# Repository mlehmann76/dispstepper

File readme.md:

# Dispense steppermotor controller
control a steppermotor to dispense fluids from syringes

4 modes

* Single Mode (dispensing on button, stop + retract after steps, selectable number of steps)
* Repeat Mode (continue dispense on pressed button, retract after button release, selectable number of steps)
* Manual Mode (control direction of stepper motor, selectable speed)
* External Mode (contro over usb serial device)

## Configuration
### By Button
push mode button, selected mode led will lit and settings can be changed by up/down button and led will switch to bar mode showning actual setting (0..3)
### By serial commands
all commands can change to read mode by adding a ?
| Command | Range | Description |
| :-- | :-- | :-- |
| *IDN | | read device version |
| SETup:FACtory:DEFault| 1 |set config to factory defaults |
| SETup:MODE | (0 .. 3) | get / set Mode / Single=0/Repeat=1/Manual=2/External=3 |
| SETup:SINGle:INDex |(0..3) | get / set single mode index |
| SETup:SINGle:VALue# |(0..4096)| get / set single mode value (# is 0..3)  steps |
| SETup:REPeat:INDex |(0..3)| get / set repeat mode index  |
| SETup:REPeat:VALue# |(0..4096)|get / set repeat mode value (# is 0..3) steps |
| SETup:MANual:INDex |(0..3)| get / set manual mode index  |
| SETup:MANual:VALue# |(0..1.0)| get / set manual mode value (# is 0..3) speed |
| SETup:EXTernal:SPeed |(0..1.0)| get / set speed value  for control over serial |
| SETup:EXTernal:STeps |(0..4096)| get / set steps value for control over serial |
| SETup:EXTernal:DIR |(-1, 0, 1)| get / set direction  for control over serial, this will start move if direction not 0. set to 0 after steps |
# Programming
## BootLoader
change into uf2-samdx1
> make BOARD=dispstepper jlink-flash
* now LED D2 should blink
## Application
### via uf2 bootloader
* double tap reset to enter boot loader
* led2 will start blinking
* the board will register as a mass storage device
* put the uf2 update file onto the mass storage and firware update will start

# License
See Microchip / Atmel / Arm source code files for license.

The new code is licensed under MIT.

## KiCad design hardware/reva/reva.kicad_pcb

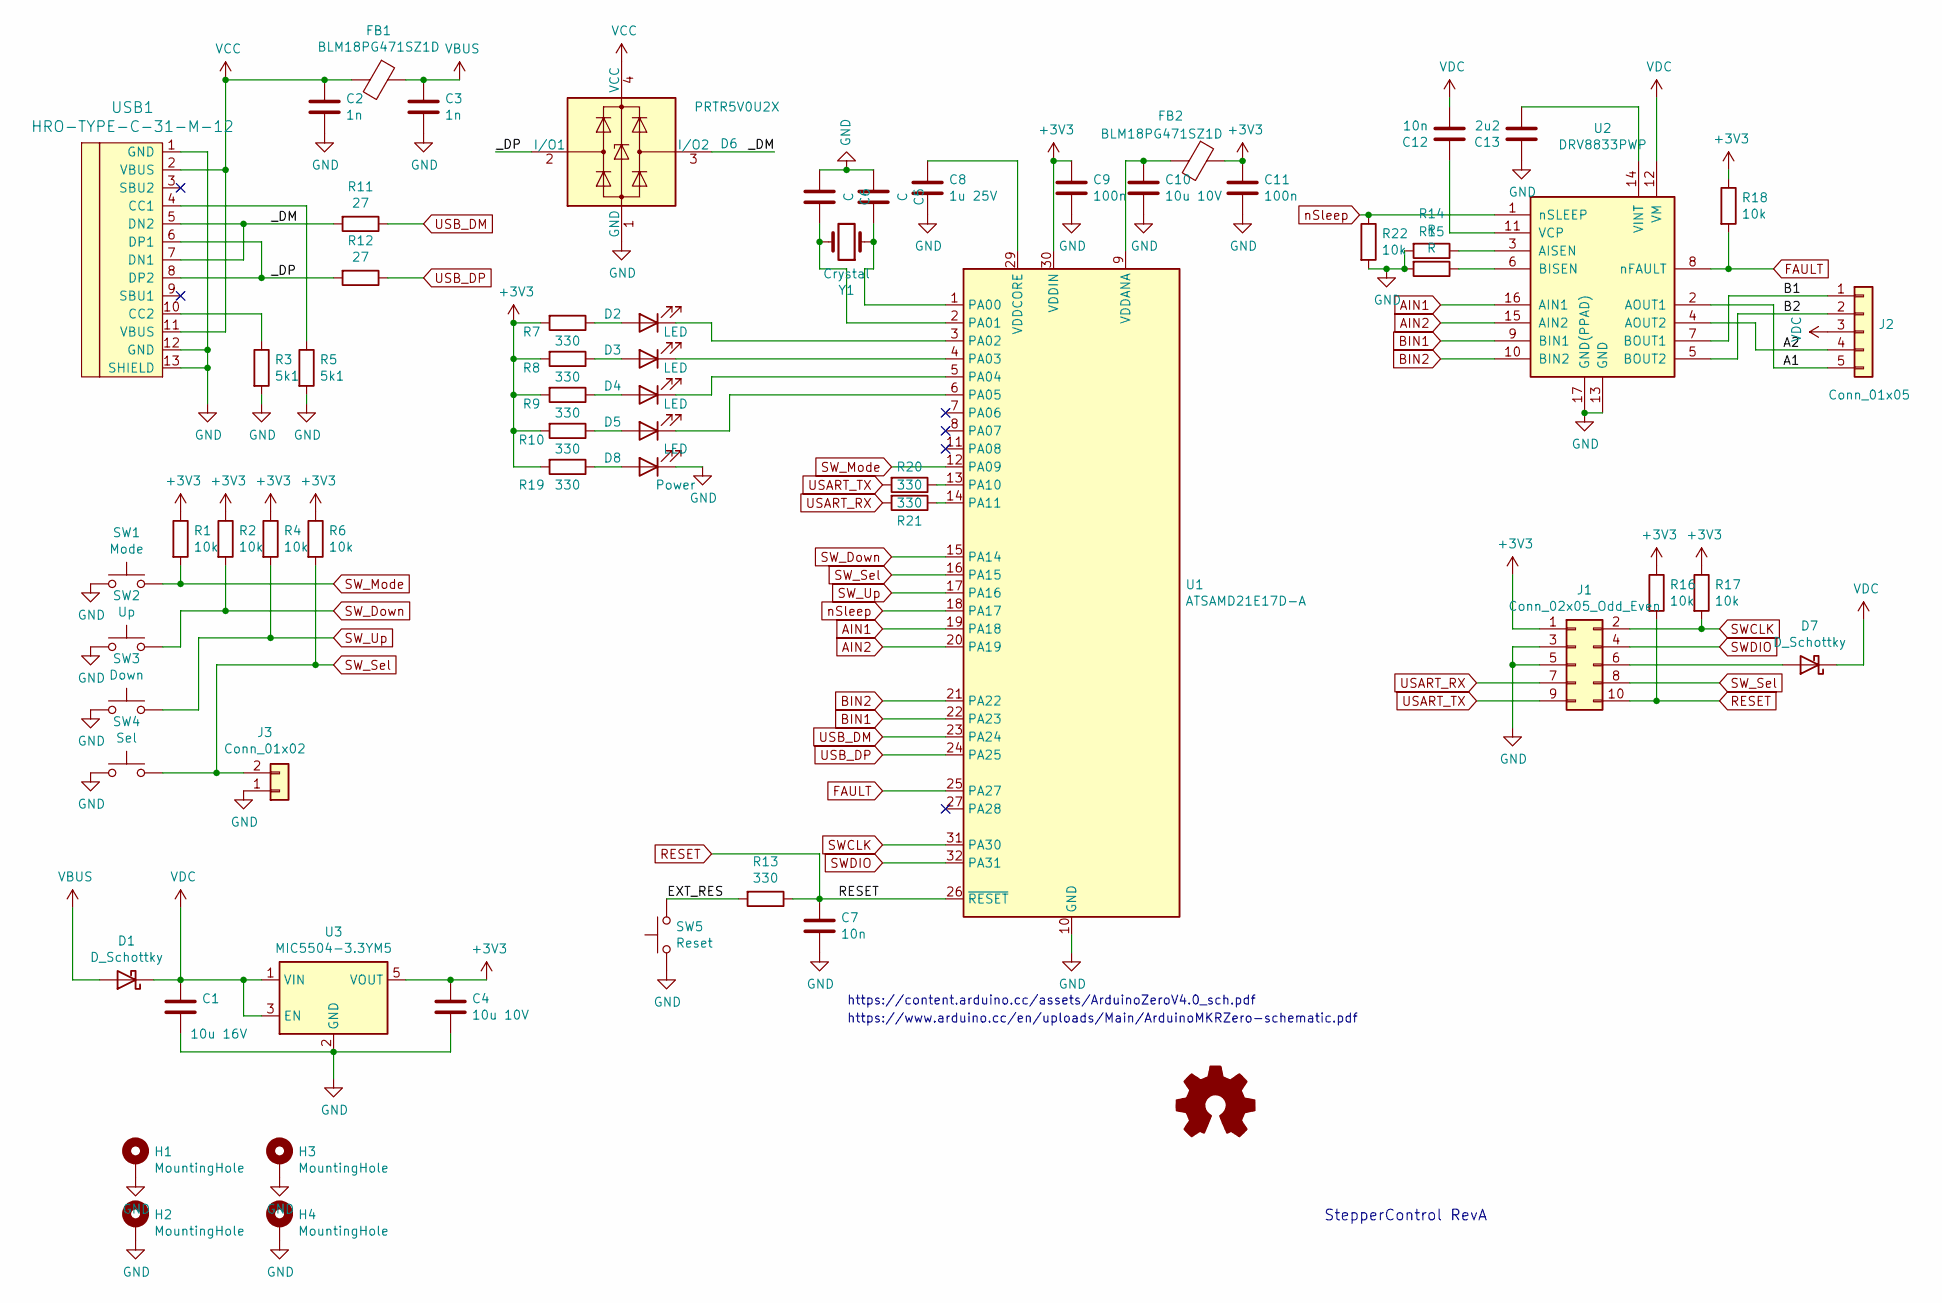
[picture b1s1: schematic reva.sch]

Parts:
C1: 10u 16V; C_0603_1608Metric
C2, C3: 1n; C_0603_1608Metric
C4, C10: 10u 10V; C_0603_1608Metric
C5, C6: C; C_0603_1608Metric
C7, C12: 10n; C_0603_1608Metric
C8: 1u 25V; C_0603_1608Metric
C9, C11: 100n; C_0603_1608Metric
C13: 2u2; C_0603_1608Metric
D1, D7: D_Schottky; D_SMA
D2, D3, D4, D5: LED; LED_0603_1608Metric
D6: PRTR5V0U2X; SOT-143
D8: Power; LED_0603_1608Metric
FB1, FB2: BLM18PG471SZ1D; L_0603_1608Metric
H1, H2, H3, H4: MountingHole; MountingHole_3.2mm_M3_DIN965_Pad
J1: Conn_02x05_Odd_Even; PinHeader_2x05_P2.54mm_Horizontal
J2: Conn_01x05; PinHeader_1x05_P2.54mm_Vertical
J3: Conn_01x02; PinHeader_1x02_P2.54mm_Vertical
R1, R2, R4, R6, R16, R17, R18, R22: 10k; R_0603_1608Metric
R3, R5: 5k1; R_0603_1608Metric
R7, R8, R9, R10, R13, R19, R20, R21: 330; R_0603_1608Metric
R11, R12: 27; R_0603_1608Metric
R14, R15: R; R_0603_1608Metric
SW1: Mode; PTS636_SMT_G
SW2: Up; PTS636_SMT_G
SW3: Down; PTS636_SMT_G
SW4: Sel; PTS636_SMT_G
SW5: Reset; PTS636_SMT_G
U1: ATSAMD21E17D-A; TQFP-32_7x7mm_P0.8mm
U2: DRV8833PWP; HTSSOP-16-1EP_4.4x5mm_P0.65mm_EP3.4x5mm_Mask2.46x2.31mm_The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
U3: MIC5504-3.3YM5; SOT-23-5
USB1: HRO-TYPE-C-31-M-12
Y1: Crystal; Crystal_SMD_2012-2Pin_2.0x1.2mm_HandSoldering

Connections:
+3V3: C4.1, C9.1, C11.1, FB2.1, J1.1, R1.1, R2.1, R4.1, R6.1, R7.2, R8.2, R9.2, R10.2, R16.1, R17.1, R18.1, R19.2, U1.30 (VDDIN), U3.5 (VOUT)
/A1: J2.5, U2.2 (AOUT1)
/A2: J2.4, U2.4 (AOUT2)
/B1: J2.1, U2.7 (BOUT1)
/B2: J2.2, U2.5 (BOUT2)
/EXT_RES: R13.2, SW5.2
/_DM: D6.3 (I/O2), R11.2, USB1.5 (DN2), USB1.7 (DN1)
/_DP: D6.2 (I/O1), R12.2, USB1.6 (DP1), USB1.8 (DP2)
AIN1: U1.19 (PA18), U2.16 (AIN1)
AIN2: U1.20 (PA19), U2.15 (AIN2)
BIN1: U1.22 (PA23), U2.9 (BIN1)
BIN2: U1.21 (PA22), U2.10 (BIN2)
FAULT: R18.2, U1.25 (PA27), U2.8 (nFAULT)
GND: C1.2, C2.2, C3.2, C4.2, C5.2, C6.2, C7.2, C8.2, C9.2, C10.2, C11.2, C13.1, D6.1 (GND), D8.1 (K), H1.1, H2.1, H3.1, H4.1, J1.3, J1.5, J3.1, R3.2, R5.2, R14.2, R15.2, R22.2, SW1.1, SW2.1, SW3.1, SW4.1, SW5.1, U1.10 (GND), U1.28 (GND), U2.13 (GND), U2.17 (GND(PPAD)), U3.2 (GND), USB1.1 (GND), USB1.12 (GND), USB1.13 (SHIELD)
unnamed: C5.1, U1.1 (PA00), Y1.1
unnamed: C6.1, U1.2 (PA01), Y1.2
unnamed: C8.1, U1.29 (VDDCORE)
unnamed: C10.1, FB2.2, U1.9 (VDDANA)
unnamed: C12.1, U2.11 (VCP)
unnamed: C13.2, U2.14 (VINT)
unnamed: D2.1 (K), U1.3 (PA02)
unnamed: D2.2 (A), R7.1
unnamed: D3.1 (K), U1.4 (PA03)
unnamed: D3.2 (A), R8.1
unnamed: D4.1 (K), U1.5 (PA04)
unnamed: D4.2 (A), R9.1
unnamed: D5.1 (K), U1.6 (PA05)
unnamed: D5.2 (A), R10.1
unnamed: D7.2 (A), J1.6
unnamed: D8.2 (A), R19.1
unnamed: R3.1, USB1.10 (CC2)
unnamed: R5.1, USB1.4 (CC1)
unnamed: R14.1, U2.3 (AISEN)
unnamed: R15.1, U2.6 (BISEN)
unnamed: R20.1, U1.13 (PA10)
unnamed: R21.1, U1.14 (PA11)
RESET: C7.1, J1.10, R13.1, R16.2, U1.26 (~RESET)
SWCLK: J1.2, R17.2, U1.31 (PA30)
SWDIO: J1.4, U1.32 (PA31)
SW_Down: R2.2, SW2.2, U1.15 (PA14)
SW_Mode: R1.2, SW1.2, U1.12 (PA09)
SW_Sel: J1.8, J3.2, R6.2, SW4.2, U1.16 (PA15)
SW_Up: R4.2, SW3.2, U1.17 (PA16)
USART_RX: J1.7, R21.2
USART_TX: J1.9, R20.2
USB_DM: R11.1, U1.23 (PA24)
USB_DP: R12.1, U1.24 (PA25)
VBUS: C3.1, D1.2 (A), FB1.1
VCC: C2.1, D6.4 (VCC), FB1.2, USB1.2 (VBUS), USB1.11 (VBUS)
VDC: C1.1, C12.2, D1.1 (K), D7.1 (K), J2.3, U2.12 (VM), U3.1 (VIN), U3.3 (EN)
nSleep: R22.1, U1.18 (PA17), U2.1 (nSLEEP)

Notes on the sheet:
https://content.arduino.cc/assets/ArduinoZeroV4.0_sch.pdf
https://www.arduino.cc/en/uploads/Main/ArduinoMKRZero-schematic.pdf
StepperControl RevA

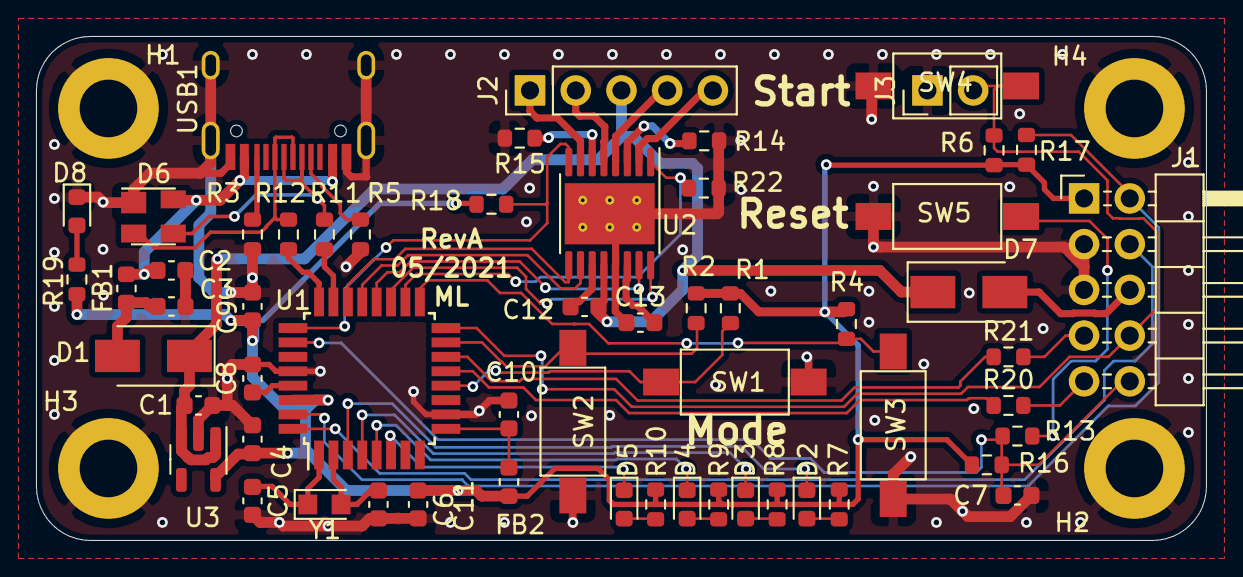
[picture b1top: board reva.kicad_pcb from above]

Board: 2 copper layers, 65.0 x 28.0 mm, 62 parts (0 on the bottom side), 51 nets.

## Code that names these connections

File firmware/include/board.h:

#ifndef _BOARD_MAIN_H_
#define _BOARD_MAIN_H_

#ifdef __cplusplus
extern "C" {
#endif

#include <stdint.h>

#define GPIO(port, pin) ((((port)&0x7u) << 5) + ((pin)&0x1Fu))
#define GPIO_PORTA 0

#define LED2 GPIO(GPIO_PORTA, 2)
#define LED3 GPIO(GPIO_PORTA, 3)
#define LED4 GPIO(GPIO_PORTA, 4)
#define LED5 GPIO(GPIO_PORTA, 5)
#define SW_MODE GPIO(GPIO_PORTA, 9)
#define PA10 GPIO(GPIO_PORTA, 10)
#define PA11 GPIO(GPIO_PORTA, 11)
#define SW_DOWN GPIO(GPIO_PORTA, 14)
#define SW_SEL GPIO(GPIO_PORTA, 15)
#define SW_UP GPIO(GPIO_PORTA, 16)
#define nSLEEP GPIO(GPIO_PORTA, 17)
#define AIN1 GPIO(GPIO_PORTA, 18)
#define AIN2 GPIO(GPIO_PORTA, 19)
#define BIN2 GPIO(GPIO_PORTA, 22)
#define BIN1 GPIO(GPIO_PORTA, 23)
#define PA24 GPIO(GPIO_PORTA, 24)
#define PA25 GPIO(GPIO_PORTA, 25)
#define nFAULT GPIO(GPIO_PORTA, 27)

void SysTick_Init(uint32_t cpuFreq);
uint32_t getTick();
void board_init();
void wrap_nv_storage_init();
int32_t wrap_nv_storage_read(const uint16_t id, const uint16_t offset,
                             uint8_t *const data, const uint16_t size);
uint16_t wrap_nv_storage_item_size(const uint16_t id);
int32_t wrap_nv_storage_write(const uint16_t id, const uint16_t offset,
                              const uint8_t *const data, const uint16_t size);
void wrap_gpio_set_pin_level(const uint8_t pin, const bool level);
bool wrap_gpio_get_pin_level(const uint8_t pin) ;
uint16_t readCounter();

#ifdef __cplusplus
}
#endif

#endif // !_BOARD_MAIN_H_

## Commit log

2021-04-27 initial
2021-04-28 schema update
2021-04-29 pcb placement
2021-04-30 connections
2021-05-02 layout final
2021-05-02 added con for Sel, added gerber
2021-06-05 initial samd21 version
2021-06-05 hardware update
2021-06-06 added cdc_acm, butoon check class
2021-06-07 add led and mode handling
2021-06-09 added control class, moved header to include
2021-06-10 added control functionality
2021-06-11 added cmake helper
2021-07-09 fixed button handling and timer
2021-07-09 fixed cmake files
2021-07-09 updated start adr to 0x2000
2021-07-10 add nv based config read functions
2021-07-11 default values for config, added config write
2021-07-20 old code cleanup
2021-07-20 cmake files changes to support compiler in path
2021-07-20 cmakelists update
2021-07-20 removed lto in Release mode
2021-07-20 Update cmake.yml
    update compiler release
2021-07-21 added bin2uf2.js to repo
2021-07-21 updated cmake.yml
2021-08-01 added cdc example, simplaeparser
2021-08-02 split action to buidl/release
2021-08-03 added cmdparse/usb_cdc initial
2021-08-04 simpleparser update
2021-08-08 move simpleparser into project, added usb cdc wrapper, change cmd parser
2021-08-11 added first cdc commands and helper functions
2021-08-13 cmdparse: more template usage
2021-08-14 added typetraits for config enums, template based
2021-08-15 added more scpi commands
2021-08-16 added mode/led update after config change
2021-08-18 revert to 10-2020-q4
2021-08-19 updated toolchain file
2021-08-19 switch build target to minsizerel
2021-08-20 fixed missing foat support
2021-08-23 added version info
2021-08-23 changed version to 0.1.0
2021-08-24 Version extract from git tag, enabled config write
2021-09-06 changes to support clang, unwind still required
2022-03-07 fixed config bug
2022-03-08 fixed config, fixed simpleparser, added control over usb, added readme
2022-03-08 add pic
2022-03-08 add pic to readme
2022-03-08 Create LICENSE
2022-03-14 added iSerial, changed usb dep
2022-03-14 added missing files
2022-03-14 gitignore update
